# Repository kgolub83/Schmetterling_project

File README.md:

# Schmetterling Project
Looping Louie on steroids, the game upgrade project

## Overview
A DC motor drives the game. Up to 8 players each have a **User Module**
with two buttons, UP and DOWN, that raise or lower that player's speed
request. The **Main Controller** (Schmetterling_MB, STM32F103C8) polls
all modules round robin over I2C. It adds up the requests of all healthy
modules and runs the motor at the resulting target speed.

```
User Module 0..7  --I2C 400 kHz-->  Main Controller  --3-phase PWM-->  Motor
(2 buttons, health)                 (sum, ramp, ctrl)
```

- **Main Controller HW:** 24 V input, 3 half-bridges (IRS2103 + N-MOSFETs),
  per-phase current sensing, USB-C debug UART, I2C bus to the User Modules
  through a level shifter.
- **I2C:** module address `0x20 + ID` (0x20..0x27). Each poll reads 1 byte:
  `HLTH | ALIVE | PAR | SPEED_REQ[4:0]`. A module with health = 0, a frozen
  ALIVE bit, a parity error or a missing ACK does not count.
- **Scheduling:** 1 ms system tick. Each tick polls one module (~51 us at
  400 kHz), so all 8 modules are polled every 8 ms.

## Folder structure
```
Schmetterling_project/
├── HW/                             Hardware
│   ├── hw_arch_description.txt     Main Controller board functional description
│   └── schmetterling_mb/           KiCad project of the Main Controller board
├── SW/                             Software
│   ├── sw_arch_description.txt     SW architecture, I2C protocol, scheduling
│   ├── MainController/             Firmware for the Main Controller (STM32F103C8)
│   └── UserModule/                 Firmware for the User Module (I2C slave)
├── LICENSE                         MIT-beer extended license
└── README.md
```

## Documentation
- [HW/hw_arch_description.txt](HW/hw_arch_description.txt): power supply,
  power stage, sensing, MCU pinout, interfaces
- [SW/sw_arch_description.txt](SW/sw_arch_description.txt): SW layers, I2C
  addressing and frame, request validation, speed calculation, 1 ms scheduler

## License
MIT-beer extended, see [LICENSE](LICENSE).

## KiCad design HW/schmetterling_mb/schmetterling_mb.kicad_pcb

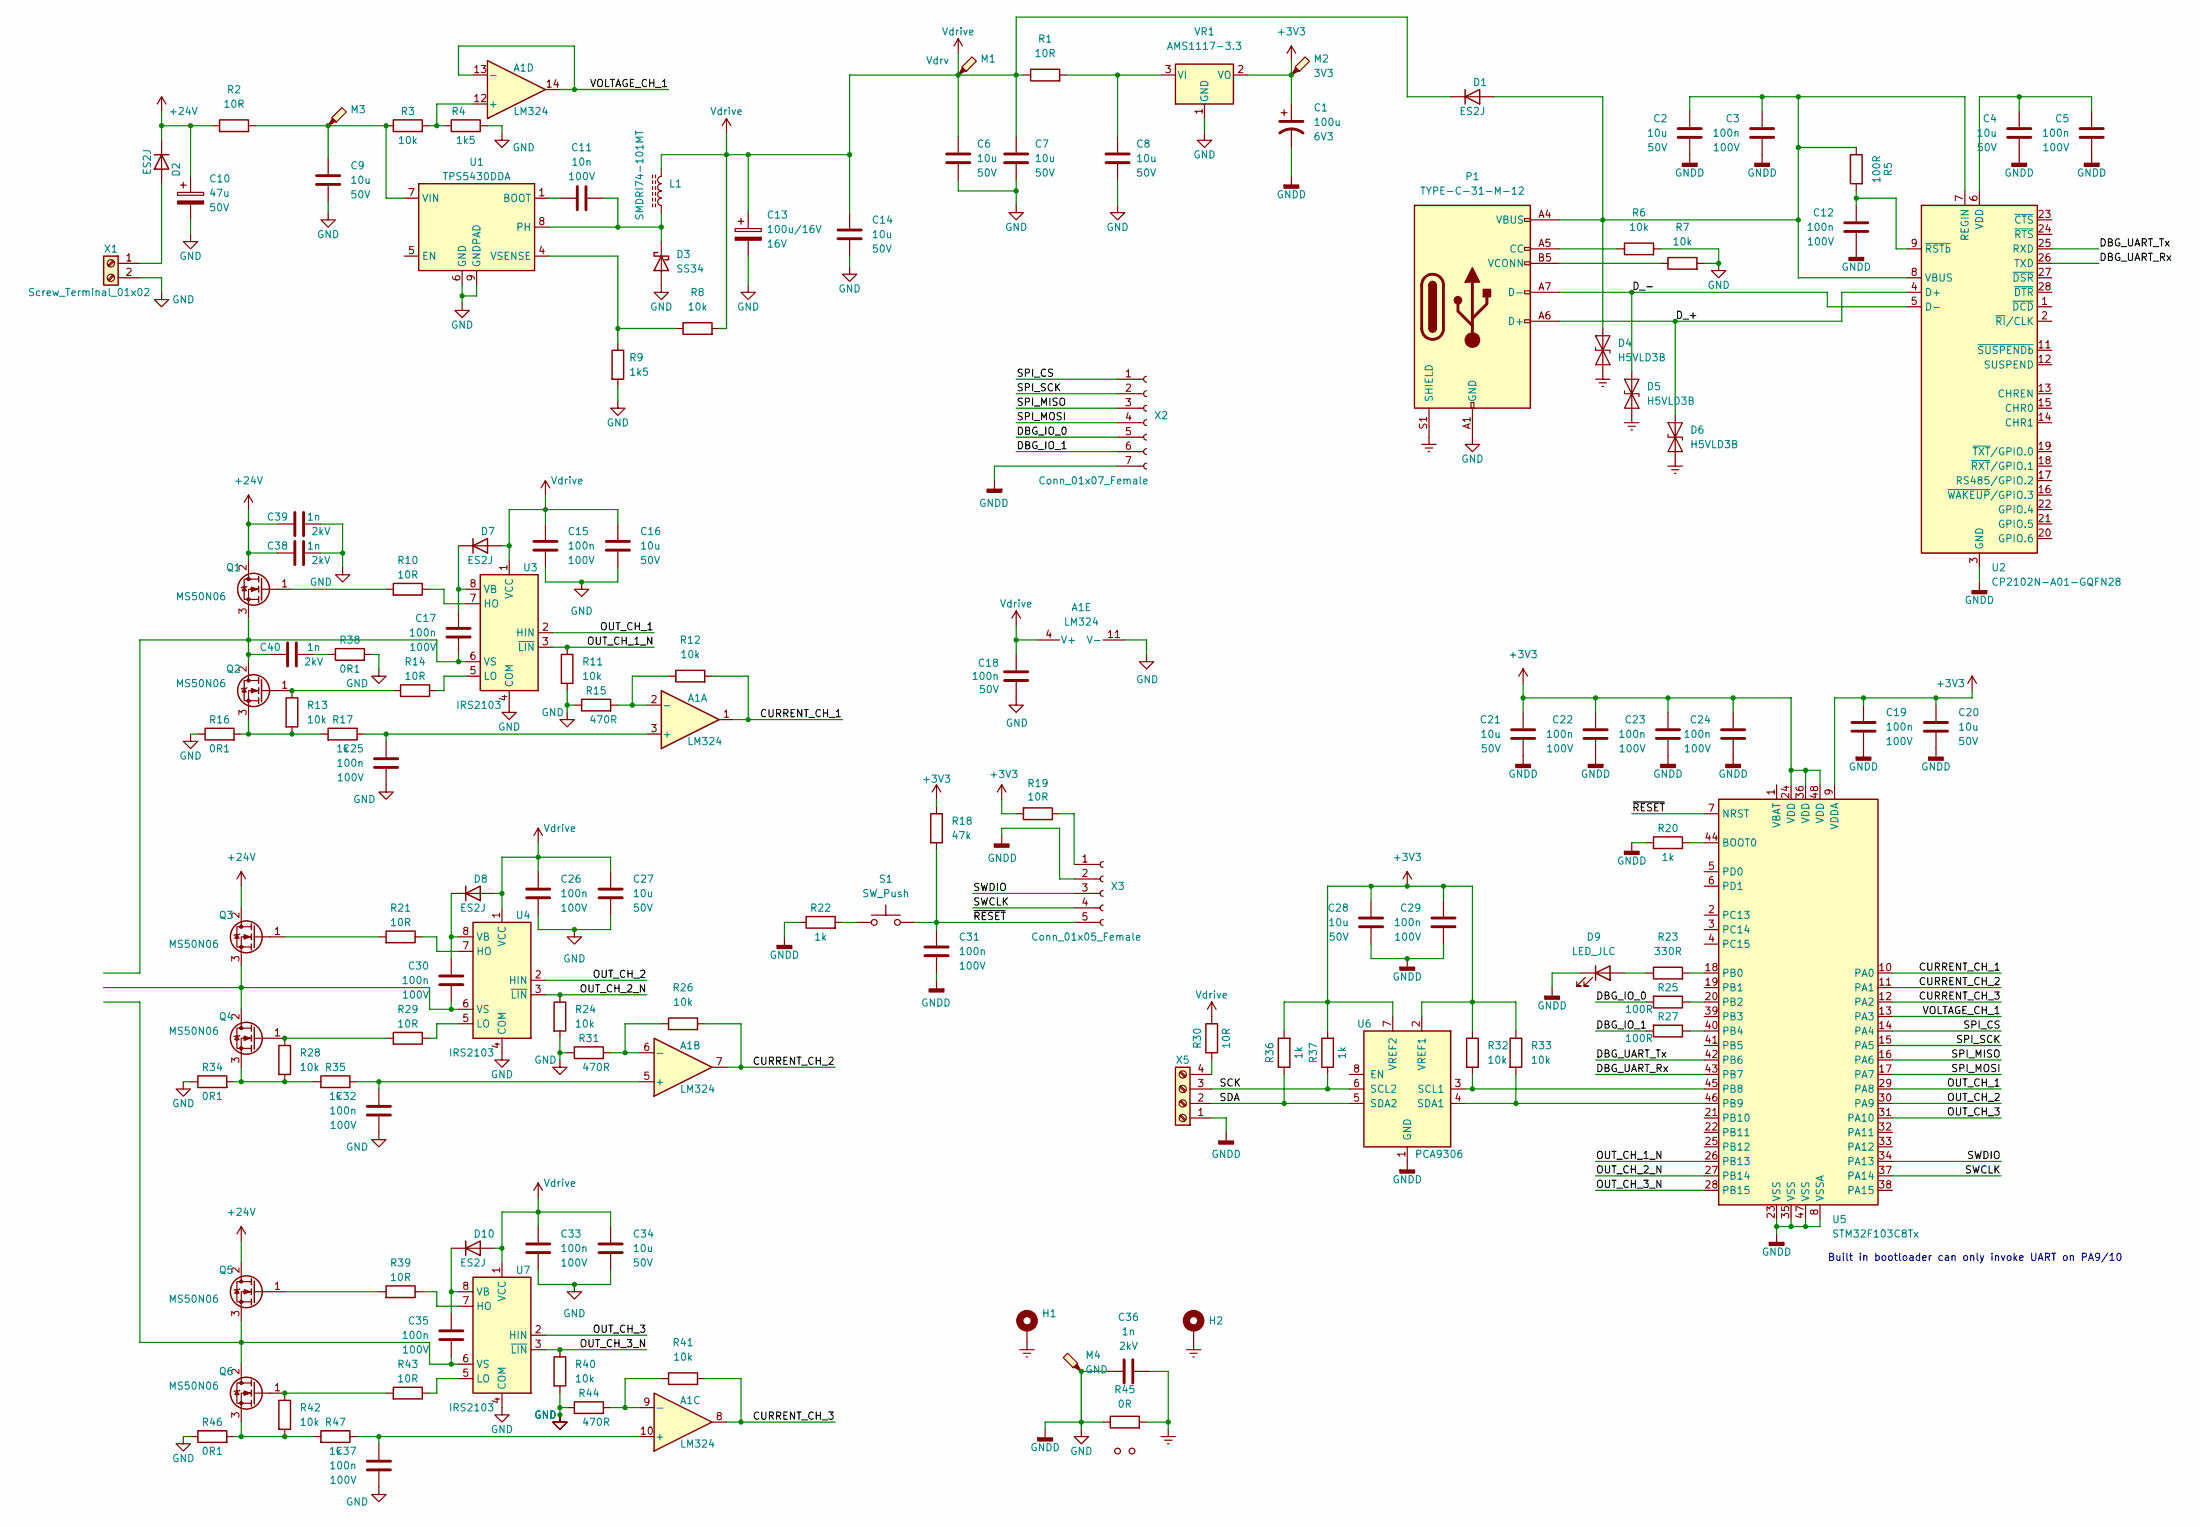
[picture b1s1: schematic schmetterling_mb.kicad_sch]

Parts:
A1: LM324; SOIC-14_3.9x8.7mm_P1.27mm; JLC_Id C71035
C1: 100u; CP_EIA-3528-21_Kemet-B_Pad1.50x2.35mm_HandSolder; Voltage 6V3; JLC_Id C16133
C2, C4, C16, C20, C21, C27, C28, C34: 10u; C_0805_2012Metric_Pad1.18x1.45mm_HandSolder; Voltage 50V; JLC_Id C15850
C3, C5, C12, C15, C17, C19, C22, C23, C24, C25, C26, C29, C30, C31, C32, C33, C35, C37: 100n; C_0805_2012Metric_Pad1.18x1.45mm_HandSolder; Voltage 100V; JLC_Id C28233
C6, C7, C8, C9, C14: 10u; C_1206_3216Metric_Pad1.33x1.80mm_HandSolder; Voltage 50V; JLC_Id C13585
C10: 47u; CP_Radial_D8.0mm_P3.50mm; Voltage 50V
C11: 10n; C_0805_2012Metric_Pad1.18x1.45mm_HandSolder; Voltage 100V; JLC_Id C1710
C13: 100u/16V; CP_Radial_D5.0mm_P2.00mm; Voltage 16V
C18: 100n; C_0805_2012Metric_Pad1.18x1.45mm_HandSolder; Voltage 50V; JLC_Id C49678
C36, C38, C39, C40: 1n; C_1206_3216Metric_Pad1.33x1.80mm_HandSolder; Voltage 2kV; JLC_Id C9196
D1, D2, D7, D8, D10: ES2J; D_SMA; JLC_Id C7420341
D3: SS34; D_SMA; JLC_Id C8678
D4, D5, D6: H5VLD3B; D_SOD-323; JLC_Id C20615805
D9: LED_JLC; LED_0805_2012Metric_Pad1.15x1.40mm_HandSolder; JLC_Id C34499
FID1, FID2: Fid_mark; Fiducial_1mm_Mask3mm
H1, H2: MountingHole_Pad; MountingHole_DB_M3__Pad
L1: SMDRI74-101MT; SMDRI74-471MT; JLC_Id C36970
M1: Vdrv; TestPoint_THTPad_D1.5mm_Drill1.0mm
M2: 3V3; TestPoint_THTPad_D1.5mm_Drill1.0mm
M3: TestPoint_Probe; TestPoint_THTPad_D1.5mm_Drill1.0mm
M4: GND; TestPoint_THTPad_D1.5mm_Drill1.0mm
P1: TYPE-C-31-M-12; USB_C_Receptacle_Palconn_UTC16-G; JLC_Id C165948
Q1, Q2, Q3, Q4, Q5, Q6: MS50N06; TO-252-2; JLC_Id C2902884
R1, R10, R14, R19, R21, R29, R30, R39, R43: 10R; R_0805_2012Metric_Pad1.20x1.40mm_HandSolder; JLC_Id C17415
R2: 10R; R_1206_3216Metric_Pad1.30x1.75mm_HandSolder; JLC_Id C17903
R3, R6, R7, R8, R11, R12, R13, R24, R26, R28, R32, R33, R40, R41, R42: 10k; R_0805_2012Metric_Pad1.20x1.40mm_HandSolder; JLC_Id C17414
R4, R9: 1k5; R_0805_2012Metric_Pad1.20x1.40mm_HandSolder; JLC_Id C4310
R5, R25, R27: 100R; R_0805_2012Metric_Pad1.20x1.40mm_HandSolder; JLC_Id C17408
R15, R31, R44: 470R; R_0805_2012Metric_Pad1.20x1.40mm_HandSolder; JLC_Id C17710
R16, R34, R38, R46: 0R1; R_1206_3216Metric_Pad1.30x1.75mm_HandSolder; JLC_Id C25334
R17, R20, R22, R35, R36, R37, R47: 1k; R_0805_2012Metric_Pad1.20x1.40mm_HandSolder; JLC_Id C17513
R18: 47k; R_0805_2012Metric_Pad1.20x1.40mm_HandSolder; JLC_Id C17713
R23: 330R; R_0805_2012Metric_Pad1.20x1.40mm_HandSolder; JLC_Id C17630
R45: 0R; R_1206_3216Metric_Pad1.30x1.75mm_HandSolder
S1: SW_Push; SW_PUSH_6mm
U1: TPS5430DDA; TI_SO-PowerPAD-8_ThermalVias; JLC_Id C9864
U2: CP2102N-A01-GQFN28; QFN-28-1EP_5x5mm_P0.5mm_EP3.35x3.35mm; JLC_Id C6568
U3, U4, U7: IRS2103; SOIC-8_3.9x4.9mm_P1.27mm
U5: STM32F103C8Tx; LQFP-48_7x7mm_P0.5mm; JLC_Id C8734
U6: PCA9306; VSSOP-8_2.3x2mm_P0.5mm; JLC_Id C123752
VR1: AMS1117-3.3; SOT-223-3_TabPin2; JLC_Id C6186
X1: Screw_Terminal_01x02; PhoenixContact_MCV_1,5_2-G-3.81_1x02_P3.81mm_Vertical
X2: Conn_01x07_Female; PinHeader_1x07_P2.54mm_Vertical
X3: Conn_01x05_Female; PinHeader_1x05_P2.54mm_Vertical
X5: Screw_Terminal_01x04; PhoenixContact_MCV_1,5_4-G-3.81_1x04_P3.81mm_Vertical

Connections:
+3V3: C1.1, C19.1, C20.1, C21.1, C22.1, C23.1, C24.1, C28.1, C29.1, M2.1, R18.1, R19.2, R32.1, R33.1, R36.2, R37.2, U5.9 (VDDA), U5.24 (VDD), U5.36 (VDD), U5.48 (VDD), U6.2 (VREF1), U6.7 (VREF2), VR1.2 (VO)
+24V: C10.1, C38.1, C39.1, D2.1 (K), Q1.2 (D), Q3.2 (D), Q5.2 (D), R2.1
/CURRENT_CH_1: A1.1, R12.2, U5.10 (PA0)
/CURRENT_CH_2: A1.7, R26.2, U5.11 (PA1)
/CURRENT_CH_3: A1.8, R41.2, U5.12 (PA2)
/DBG_IO_0: R25.2, X2.5
/DBG_IO_1: R27.2, X2.6
/DBG_UART_Rx: U2.26 (TXD), U5.43 (PB7)
/DBG_UART_Tx: U2.25 (RXD), U5.42 (PB6)
/D_+: D6.2 (A2), P1.A6 (D+), U2.4 (D+)
/D_-: D5.2 (A2), P1.A7 (D-), U2.5 (D-)
/OUT_CH_1: U3.2 (HIN), U5.29 (PA8)
/OUT_CH_1_N: R11.1, U3.3 (~LIN), U5.26 (PB13)
/OUT_CH_2: U4.2 (HIN), U5.30 (PA9)
/OUT_CH_2_N: R24.1, U4.3 (~LIN), U5.27 (PB14)
/OUT_CH_3: U5.31 (PA10), U7.2 (HIN)
/OUT_CH_3_N: R40.1, U5.28 (PB15), U7.3 (~LIN)
/SCK: R37.1, U6.6 (SCL2), X5.3
/SDA: R36.1, U6.5 (SDA2), X5.2
/SPI_CS: U5.14 (PA4), X2.1
/SPI_MISO: U5.16 (PA6), X2.3
/SPI_MOSI: U5.17 (PA7), X2.4
/SPI_SCK: U5.15 (PA5), X2.2
/SWCLK: U5.37 (PA14), X3.4
/SWDIO: U5.34 (PA13), X3.3
/VOLTAGE_CH_1: A1.13 (-), A1.14, U5.13 (PA3)
/~RESET: C31.1, R18.2, S1.2, U5.7 (NRST), X3.5
Earth: C36.2, D4.1 (A1), D5.1 (A1), D6.1 (A1), H1.1, H2.1, P1.S1 (SHIELD), R45.2
GND: A1.11 (V-), C1.2, C2.2, C3.2, C4.2, C5.2, C6.2, C7.2, C8.2, C9.2, C10.2, C12.2, C13.2, C14.2, C15.2, C16.2, C18.2, C19.2, C20.2, C21.2, C22.2, C23.2, C24.2, C25.2, C26.2, C27.2, C28.2, C29.2, C31.2, C32.2, C33.2, C34.2, C36.1, C37.2, C38.2, C39.2, D3.2 (A), D9.1 (K), M4.1, P1.A1 (GND), P1.A12 (GND), P1.B1 (GND), P1.B12 (GND), R4.2, R6.2, R7.2, R9.2, R11.2, R15.1, R16.1, R20.1, R22.1, R24.2, R31.1, R34.1, R38.2, R40.2, R44.1, R45.1, R46.1, U1.6 (GND), U1.9 (GNDPAD), U2.3 (GND), U2.29 (GND), U3.4 (COM), U4.4 (COM), U5.8 (VSSA), U5.23 (VSS), U5.35 (VSS), U5.47 (VSS), U6.1 (GND), U7.4 (COM), VR1.1 (GND), X1.2, X2.7, X3.2, X5.1
unnamed: A1.2 (-), R12.1, R15.2
unnamed: A1.3 (+), C25.1, R17.1
unnamed: A1.5 (+), C32.1, R35.1
unnamed: A1.6 (-), R26.1, R31.2
unnamed: A1.9 (-), R41.1, R44.2
unnamed: A1.10 (+), C37.1, R47.1
unnamed: A1.12 (+), R3.2, R4.1
unnamed: C2.1, C3.1, D1.2 (A), D4.2 (A2), P1.A4 (VBUS), P1.A9 (VBUS), P1.B4 (VBUS), P1.B9 (VBUS), R5.1, U2.7 (REGIN), U2.8 (VBUS)
unnamed: C4.1, C5.1, U2.6 (VDD)
unnamed: C8.1, R1.2, VR1.3 (VI)
unnamed: C9.1, M3.1, R2.2, R3.1, U1.7 (VIN)
unnamed: C11.1, U1.1 (BOOT)
unnamed: C11.2, D3.1 (K), L1.1, U1.8 (PH)
unnamed: C12.1, R5.2, U2.9 (~RSTb)
unnamed: C17.1, D7.1 (K), U3.8 (VB)
unnamed: C17.2, C40.1, Q1.3 (S), Q2.2 (D), U3.6 (VS)
unnamed: C30.1, D8.1 (K), U4.8 (VB)
unnamed: C30.2, Q3.3 (S), Q4.2 (D), U4.6 (VS)
unnamed: C35.1, D10.1 (K), U7.8 (VB)
unnamed: C35.2, Q5.3 (S), Q6.2 (D), U7.6 (VS)
unnamed: C40.2, R38.1
unnamed: D2.2 (A), X1.1
unnamed: D9.2 (A), R23.1
unnamed: P1.A5 (CC), R6.1
unnamed: P1.B5 (VCONN), R7.1
unnamed: Q1.1 (G), R10.2
unnamed: Q2.1 (G), R13.1, R14.2
unnamed: Q2.3 (S), R13.2, R16.2, R17.2
unnamed: Q3.1 (G), R21.2
unnamed: Q4.1 (G), R28.1, R29.2
unnamed: Q4.3 (S), R28.2, R34.2, R35.2
unnamed: Q5.1 (G), R39.2
unnamed: Q6.1 (G), R42.1, R43.2
unnamed: Q6.3 (S), R42.2, R46.2, R47.2
unnamed: R8.1, R9.1, U1.4 (VSENSE)
unnamed: R10.1, U3.7 (HO)
unnamed: R14.1, U3.5 (LO)
unnamed: R19.1, X3.1
unnamed: R20.2, U5.44 (BOOT0)
unnamed: R21.1, U4.7 (HO)
unnamed: R22.2, S1.1
unnamed: R23.2, U5.18 (PB0)
unnamed: R25.1, U5.20 (PB2)
unnamed: R27.1, U5.40 (PB4)
unnamed: R29.1, U4.5 (LO)
unnamed: R30.2, X5.4
unnamed: R32.2, U5.45 (PB8), U6.3 (SCL1)
unnamed: R33.2, U5.46 (PB9), U6.4 (SDA1)
unnamed: R39.1, U7.7 (HO)
unnamed: R43.1, U7.5 (LO)
Vdrive: A1.4 (V+), C6.1, C7.1, C13.1, C14.1, C15.1, C16.1, C18.1, C26.1, C27.1, C33.1, C34.1, D1.1 (K), D7.2 (A), D8.2 (A), D10.2 (A), L1.2, M1.1, R1.1, R8.2, R30.1, U3.1 (VCC), U4.1 (VCC), U7.1 (VCC)

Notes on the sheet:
Built in bootloader can only invoke UART on PA9/10

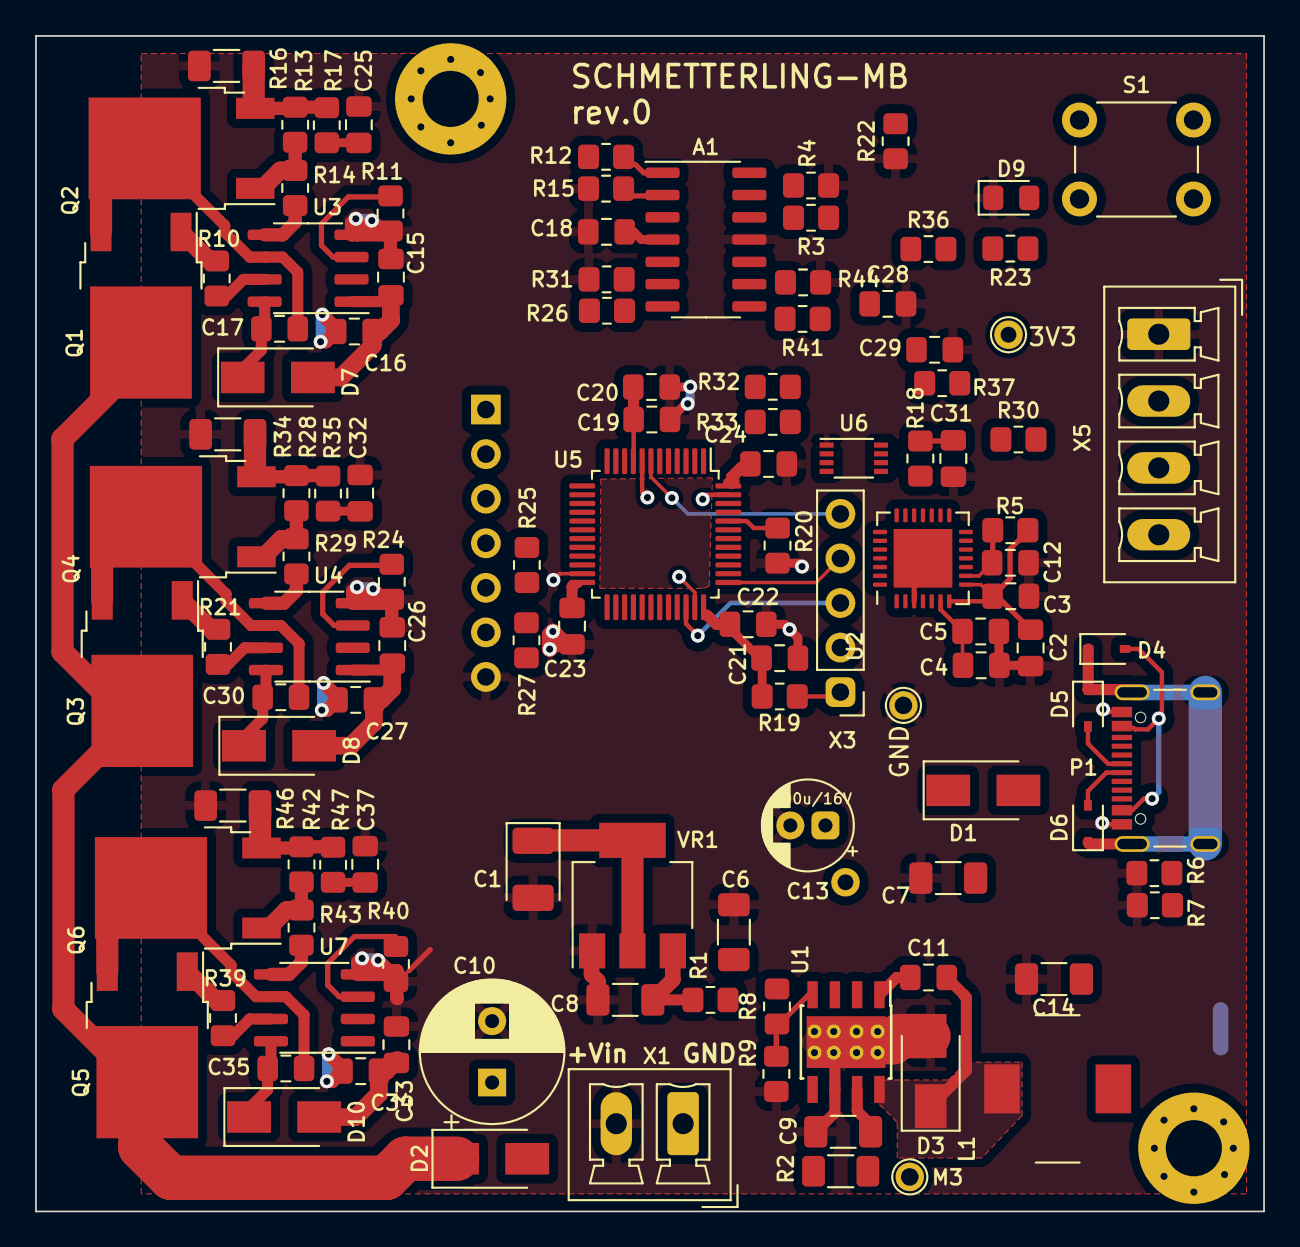
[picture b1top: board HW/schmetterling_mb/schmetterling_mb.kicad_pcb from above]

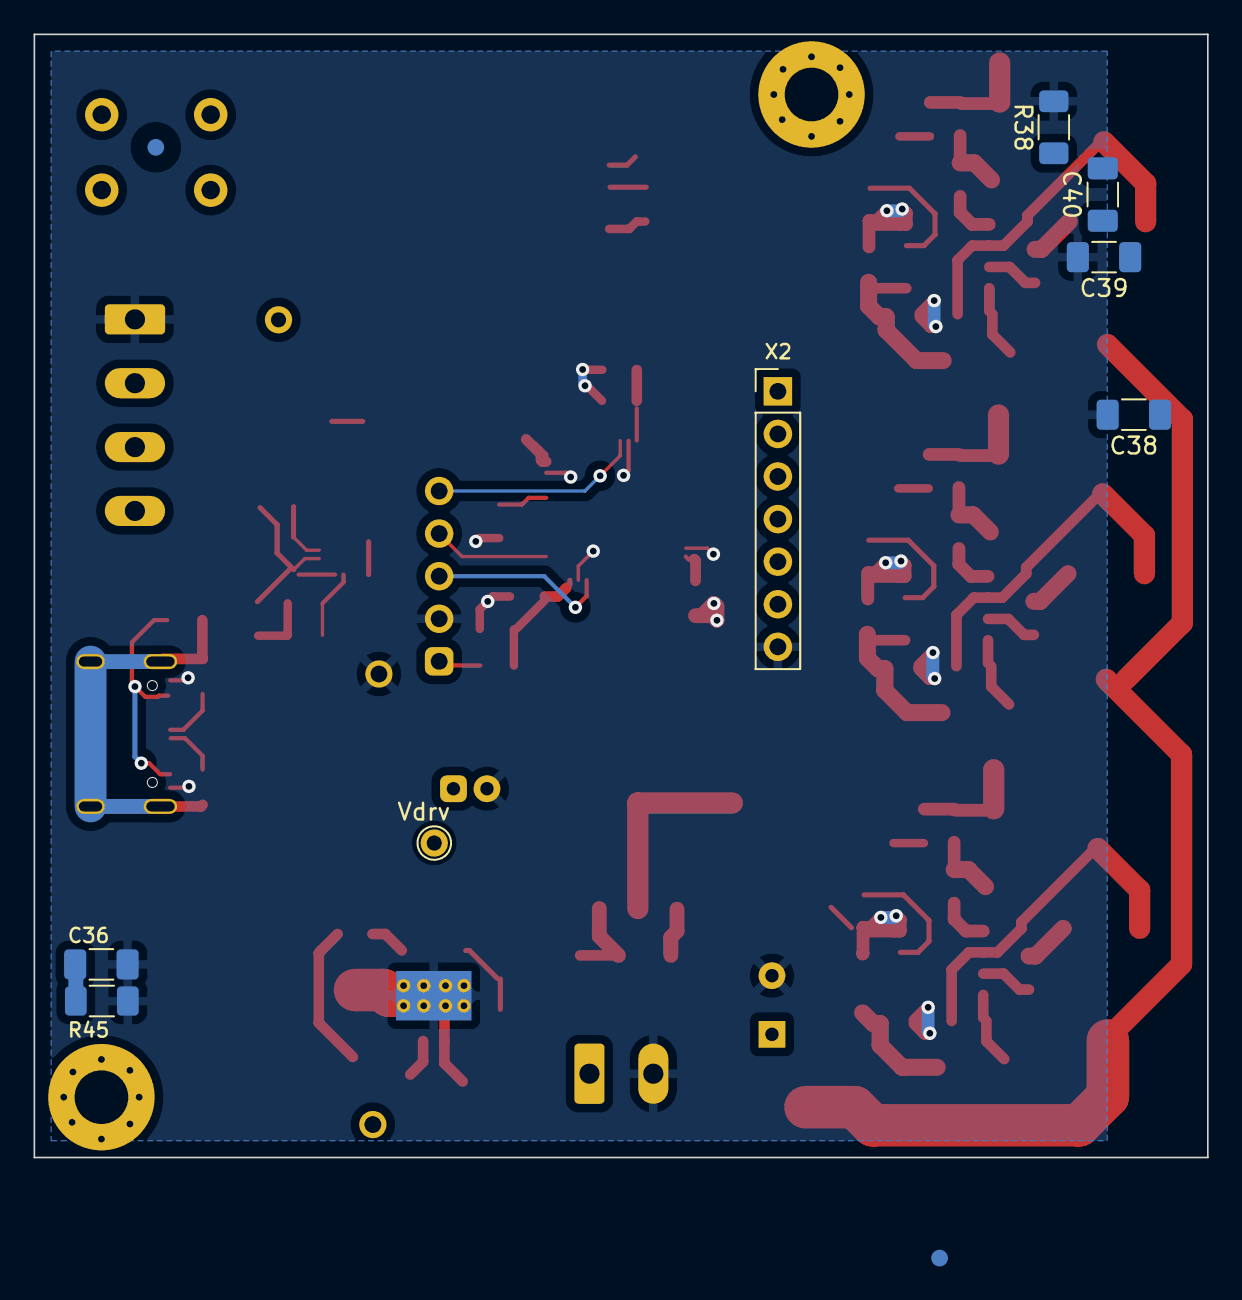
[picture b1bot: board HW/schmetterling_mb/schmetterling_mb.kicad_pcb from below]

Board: 2 copper layers, 70.0 x 67.0 mm, 127 parts (10 on the bottom side), 80 nets.

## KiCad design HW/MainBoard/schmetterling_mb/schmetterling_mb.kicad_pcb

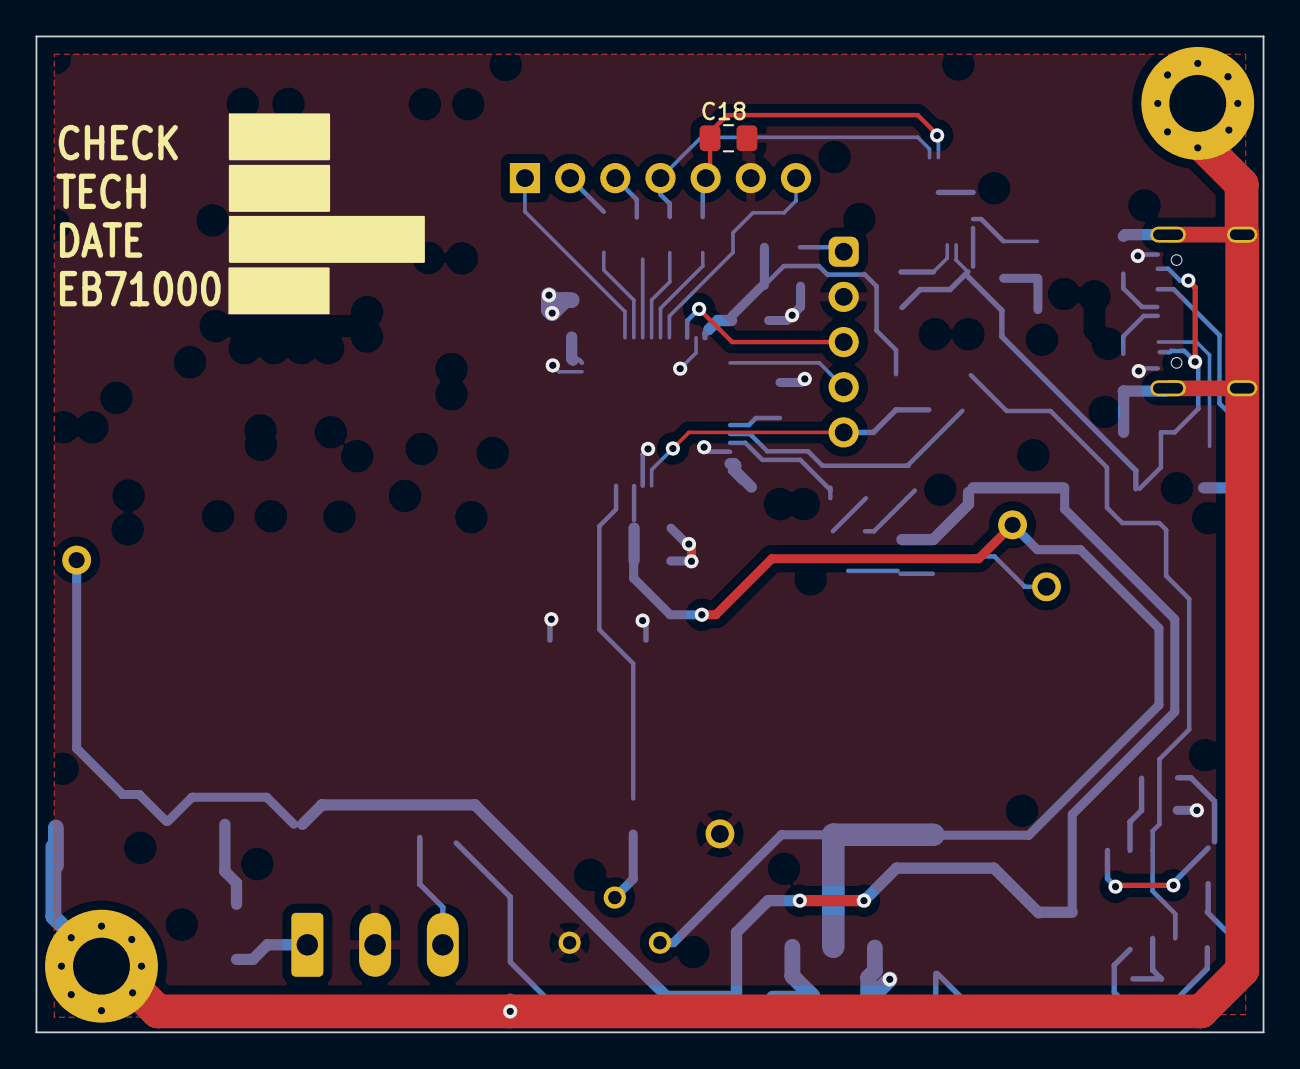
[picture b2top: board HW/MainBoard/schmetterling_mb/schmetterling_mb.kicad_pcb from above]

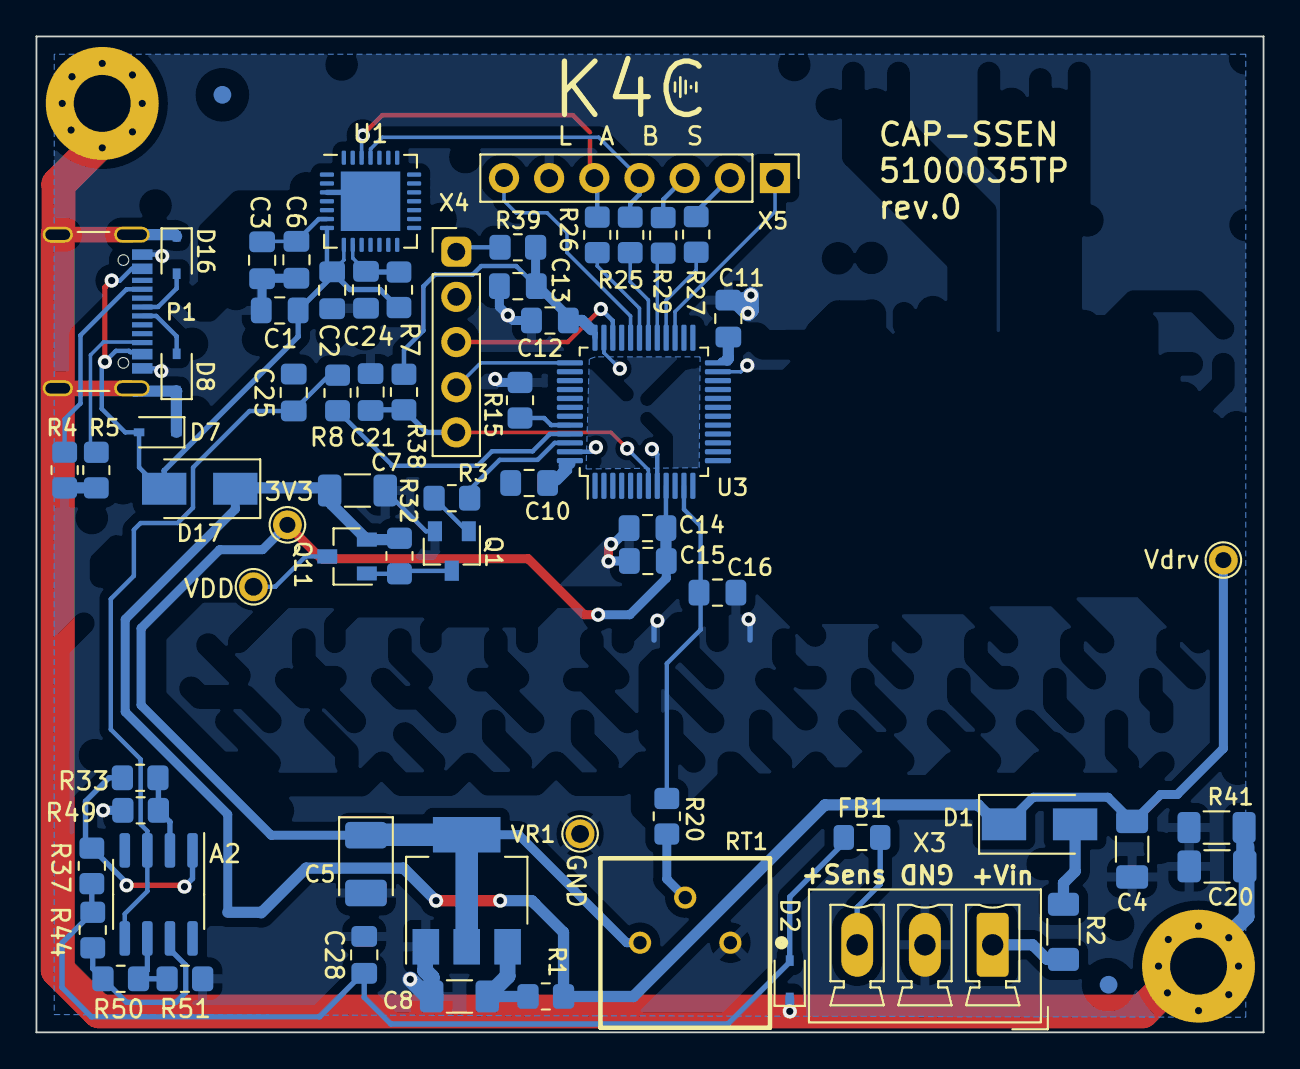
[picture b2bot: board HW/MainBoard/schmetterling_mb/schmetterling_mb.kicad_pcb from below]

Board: 2 copper layers, 69.0 x 56.0 mm, 70 parts (67 on the bottom side), 43 nets.

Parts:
A2: OPA2192; SOIC-8_3.9x4.9mm_P1.27mm
C1, C3, C13, C15, C16: 10u; C_0805_2012Metric_Pad1.18x1.45mm_HandSolder
C2, C6, C10, C11, C12, C14, C21, C24, C25, C28: 100n; C_0805_2012Metric_Pad1.18x1.45mm_HandSolder
C4, C7, C8: 10u; C_1206_3216Metric_Pad1.33x1.80mm_HandSolder
C5: 100u; CP_EIA-3528-21_Kemet-B_Pad1.50x2.35mm_HandSolder
C18: NC; C_0805_2012Metric_Pad1.18x1.45mm_HandSolder
C20: 1n; C_1206_3216Metric_Pad1.33x1.80mm_HandSolder
D1, D17: SS34; D_SMA
D2, D7, D8, D16: H5VLD3B; D_SOD-323
FB1: GZ2012D601TF; L_0805_2012Metric_Pad1.15x1.40mm_HandSolder
FID1, FID2: Fid_mark; Fiducial_1mm_Mask3mm
H1, H5: MountingHole_Pad; MountingHole_DB_M3__Pad
M1: Vdrv; TestPoint_THTPad_D1.5mm_Drill1.0mm
M2: 3V3; TestPoint_THTPad_D1.5mm_Drill1.0mm
M4: VDD; TestPoint_THTPad_D1.5mm_Drill1.0mm
M5: GND; TestPoint_THTPad_D1.5mm_Drill1.0mm
P1: TYPE-C-31-M-12; USB_C_Receptacle_Palconn_UTC16-G
Q1: 2N7002; SOT-23
Q11: AO3401A; SOT-23
R1, R39: 10R; R_0805_2012Metric_Pad1.20x1.40mm_HandSolder
R2: 10R; R_1206_3216Metric_Pad1.30x1.75mm_HandSolder
R3, R7, R25, R26, R27, R29, R37, R44: 100R; R_0805_2012Metric_Pad1.20x1.40mm_HandSolder
R4, R5: 10k; R_0805_2012Metric_Pad1.20x1.40mm_HandSolder
R8, R15, R20, R32, R33, R49, R50, R51: 1k; R_0805_2012Metric_Pad1.20x1.40mm_HandSolder
R38: 47k; R_0805_2012Metric_Pad1.20x1.40mm_HandSolder
R41: 0R; R_1206_3216Metric_Pad1.30x1.75mm_HandSolder
RT1: 3386P-1-103LF; 3386P_1
U1: CP2102N-A01-GQFN28; QFN-28-1EP_5x5mm_P0.5mm_EP3.35x3.35mm
U3: STM32F103C8Tx; LQFP-48_7x7mm_P0.5mm
VR1: AMS1117-3.3; SOT-223-3_TabPin2
X3: Screw_Terminal_01x03; PhoenixContact_MCV_1,5_3-G-3.81_1x03_P3.81mm_Vertical
X4: Conn_01x05_Female; PinHeader_1x05_P2.54mm_Vertical
X5: Conn_01x07_Female; PinHeader_1x07_P2.54mm_Vertical

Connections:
+3V3: C5.1, C10.1, C11.1, C12.1, C13.1, C14.1, C15.1, M2.1, R38.1, R39.2, RT1.3, U3.9 (VDDA), U3.24 (VDD), U3.36 (VDD), U3.48 (VDD), VR1.2 (VO)
/ADC1_IN1: C16.1, R20.1, U3.11 (PA1)
/BOOT: U3.27 (PB14), X5.1
/DAC_OUT: R8.1, U3.45 (PB8)
/DBG_IO_0: R27.2, X5.2
/DBG_IO_1: R29.2, X5.3
/DBG_UART_Rx: C18.1, R26.1, U1.26 (TXD), X5.5
/DBG_UART_Tx: R25.1, U1.25 (RXD), X5.4
/D_+: D16.2 (A2), P1.A6 (D+), U1.4 (D+)
/D_-: D8.2 (A2), P1.A7 (D-), U1.5 (D-)
/LED_DRV_CHN_4: R3.1, U3.46 (PB9)
/RST_ESP: U3.32 (PA11), X5.7
/SWCLK: U3.37 (PA14), X4.4
/SWDIO: U3.34 (PA13), X4.3
/~RESET: C21.1, R38.2, U3.7 (NRST), X4.5
Earth: C20.2, D2.1 (A1), D7.1 (A1), D8.1 (A1), D16.1 (A1), H1.1, H5.1, P1.S1 (SHIELD), R41.2
GND: C1.2, C2.2, C3.2, C4.2, C5.2, C6.2, C7.2, C8.2, C10.2, C11.2, C12.2, C13.2, C14.2, C15.2, C16.2, C18.2, C20.1, C21.2, C24.2, C25.2, C28.2, M5.1, P1.A1 (GND), P1.A12 (GND), P1.B1 (GND), P1.B12 (GND), Q1.2 (S), R4.2, R5.2, R15.1, R41.1, R49.2, R51.2, RT1.1, U1.3 (GND), U1.29 (GND), U3.8 (VSSA), U3.23 (VSS), U3.35 (VSS), U3.47 (VSS), VR1.1 (GND), X3.2, X4.2, X5.6
unnamed: A2.1, R33.1, R37.1
unnamed: A2.2 (-), R33.2, R49.1
unnamed: A2.3 (+), A2.5 (+), C25.1, R8.2
unnamed: A2.6 (-), R50.2, R51.1
unnamed: A2.7, R44.2, R50.1
unnamed: C1.1, C2.1, D7.2 (A2), D17.2 (A), P1.A4 (VBUS), P1.A9 (VBUS), P1.B4 (VBUS), P1.B9 (VBUS), R7.1, U1.7 (REGIN), U1.8 (VBUS)
unnamed: C3.1, C6.1, U1.6 (VDD)
unnamed: C8.1, R1.2, VR1.3 (VI)
unnamed: C24.1, R7.2, U1.9 (~RSTb)
unnamed: C28.1, D2.2 (A2), FB1.1, R37.2, R44.1
unnamed: D1.2 (A), R2.1
unnamed: FB1.2, X3.3
unnamed: P1.A5 (CC), R4.1
unnamed: P1.B5 (VCONN), R5.1
unnamed: Q1.1 (G), R3.2
unnamed: Q1.3 (D), Q11.1 (G), R32.1
unnamed: R2.2, X3.1
unnamed: R15.2, U3.44 (BOOT0)
unnamed: R20.2, RT1.2
unnamed: R25.2, U3.30 (PA9)
unnamed: R26.2, U3.31 (PA10)
unnamed: R27.1, U3.28 (PB15)
unnamed: R29.1, U3.29 (PA8)
unnamed: R39.1, X4.1
VDD: M4.1, Q11.3 (D)
Vdrive: C4.1, C7.1, D1.1 (K), D17.1 (K), M1.1, Q11.2 (S), R1.1, R32.2
